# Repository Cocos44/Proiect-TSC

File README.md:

# Proiect InkTime - Smartwatch

Un smartwatch bazat pe microcontrollerul Nordic nRF52840 cu display e-Paper.

---

## Diagrama bloc

---

## Bill of Materials

| Ref | Componenta | Valoare | JLC Parts | Datasheet |
|-----|------------|---------|-----------|-----------|
| U1 | nRF52840 | $5.14 | [JLC](https://jlcpcb.com/parts/componentSearch?searchTxt=nRF52840-QF) | [DS](https://jlcpcb.com/api/file/downloadByFileSystemAccessId/8589839228197629952) |
| SWD | TC2030-IDC | $100.26 | [JLC](https://jlcpcb.com/partdetail/MicrochipTech-TC2030_CLIP3PACK/C5444772) | [DS](https://www.lcsc.com/datasheet/lcsc_datasheet_2403201318_Microchip-Tech-TC2030-CLIP-3PACK_C5444772.pdf) |
| ANT1 | 2450AT18B100E | $1.03 | [JLC](https://jlcpcb.com/partdetail/JohansonDielectrics-2450AT18B100E/C2917717) | [DS](https://jlcpcb.com/api/file/downloadByFileSystemAccessId/8588940948130156544) |
| X1 | NX2016SA-32MHZ-EXS00A-CS11336 | $9.04 | [JLC](https://jlcpcb.com/partdetail/NDK-NX2016SA_32MHZ_EXS00ACS11336/C6134317) | [DS](https://jlcpcb.com/api/file/downloadByFileSystemAccessId/8603064888214908928) |
| L2 | RC0402JR-070RL | $0.01 | [JLC](https://jlcpcb.com/partdetail/YAGEO-RC0402JR070RL/C60485) | [DS](https://jlcpcb.com/api/file/downloadByFileSystemAccessId/8717146932348461056) |
| L3 | RC0402JR-070RL | $0.01 | [JLC](https://jlcpcb.com/partdetail/YAGEO-RC0402JR070RL/C60485) | [DS](https://jlcpcb.com/api/file/downloadByFileSystemAccessId/8717146932348461056) |
| X2 | FC-135_32.7680KA-A3 | $0.2677 | [JLC](https://jlcpcb.com/partdetail/SeikoEpson-FC_135_32_7680KAA3/C2650472) | [DS](https://jlcpcb.com/partdetail/SeikoEpson-FC_135_32_7680KAA3/C2650472) |
| IC3 | BMA423 | $11.30 | [JLC](https://jlcpcb.com/partdetail/BoschSensortec-BMA423/C189517) | [DS](https://jlcpcb.com/api/file/downloadByFileSystemAccessId/8588894317147017216) |
| IC9 | RT6160 | $0.56 | [JLC](https://jlcpcb.com/partdetail/RichtekTech-RT6160AWSC/C7065276) | [DS](https://jlcpcb.com/api/file/downloadByFileSystemAccessId/8600398231234883584) |
| L7 | MLP2016SR47MT0S1 | $0.10 | [JLC](https://jlcpcb.com/partdetail/TDK-MLP2016SR47MT0S1/C87545) | [DS](https://jlcpcb.com/api/file/downloadByFileSystemAccessId/8588933367512879104) |
| IC1 | BQ25180YBGR | $2.01 | [JLC](https://jlcpcb.com/partdetail/TexasInstruments-BQ25180YBGR/C3682423) | [DS](https://www.ti.com/cn/lit/gpn/bq25180) |
| L5 | 744043680 | $9.53 | [JLC](https://jlcpcb.com/partdetail/WurthElektronik-744043680/C2045671) | [DS](https://www.we-online.com/components/products/datasheet/744043680.pdf) |
| D2 | MBR0530 | $0.03 | [JLC](https://jlcpcb.com/partdetail/78464-MBR0530/C77336) | [DS](https://jlcpcb.com/api/file/downloadByFileSystemAccessId/8586175081181818880) |
| D4 | MBR0530 | $0.03 | [JLC](https://jlcpcb.com/partdetail/78464-MBR0530/C77336) | [DS](https://jlcpcb.com/api/file/downloadByFileSystemAccessId/8586175081181818880) |
| D5 | MBR0530 | $0.03 | [JLC](https://jlcpcb.com/partdetail/78464-MBR0530/C77336) | [DS](https://jlcpcb.com/api/file/downloadByFileSystemAccessId/8586175081181818880) |
| Q3 | SI1308EDL-T1-GE3 | $0.18 | [JLC](https://jlcpcb.com/partdetail/VishayIntertech-SI1308EDL_T1GE3/C469327) | [DS](https://jlcpcb.com/api/file/downloadByFileSystemAccessId/8588884784742846464) |
| Q1 | DMG2305UX-7 | $0.10 | [JLC](https://jlcpcb.com/partdetail/DiodesIncorporated-DMG2305UX7/C150470) | [DS](https://jlcpcb.com/api/file/downloadByFileSystemAccessId/8560079443617075200) |
| IC2 | DRV2605YZFR | $1.31 | [JLC](https://jlcpcb.com/partdetail/TexasInstruments-DRV2605YZFR/C81079) | [DS](https://www.ti.com/cn/lit/gpn/drv2605) |
| D3 | USBLC6-2SC6Y | $0.24 | [JLC](https://jlcpcb.com/partdetail/STMicroelectronics-USBLC62SC6Y/C2969755) | [DS](https://jlcpcb.com/api/file/downloadByFileSystemAccessId/8603165824304111616) |
| J4 | KH-TYPE-C-16P | $0.08 | [JLC](https://jlcpcb.com/partdetail/Shenzhen_KinghelmElec-KH_TYPE_C16P/C709357) | [DS](https://jlcpcb.com/api/file/downloadByFileSystemAccessId/8588905154556923904) |
| U3 | MAX17048G-T10 | $2.44 | [JLC](https://jlcpcb.com/partdetail/2777647-MAX17048GT10/C2682616) | [DS](https://jlcpcb.com/api/file/downloadByFileSystemAccessId/8588907428524003328) |
| J1 | 503480-2400 | $0.84 | [JLC](https://jlcpcb.com/partdetail/MOLEX-5034802400/C122434) | [DS](https://www.molex.com/content/dam/molex/molex-dot-com/products/automated/en-us/salesdrawingpdf/503/503480/5034802400_sd.pdf?inline) |

---

## Descriere Functionalitate Hardware

### Microcontroller - nRF52840
 Caracteristici principale:
- ARM Cortex-M4 la 64 MHz
- 1MB Flash, 256KB RAM
- Bluetooth 5.0 / BLE integrat
- Radio 2.4GHz cu suport pentru antena externa
- Interfete multiple: SPI, I2C, UART, GPIO
 
### Display E-Paper - Waveshare 1.54" V2
 
Display-ul comunica prin SPI pe 4 fire:
- Rezolutie: 200x200 pixeli
- Consum ultra-redus - retine imaginea fara alimentare
- Conectat la nRF52840 prin conectorul FPC 24 pini (503480-2400)
 
### IMU - BMA423
 
Accelerometrul BMA423 comunica prin I2C:
- Accelerometru pe 3 axe
- Numarare pasi, recunoastere activitate
 
### Incarcator Baterie - BQ25180
 
BQ25180 gestioneaza incarcarea bateriei prin I2C:
- Intrare: USB-C 5V
- Iesire: 3.7V LiPo
- Curent maxim de incarcare: 250mA
 
### Baterie - AKYGA LP502030
 
- Dimensiuni: 32.5mm x 21mm x 5.5mm
- Conectata direct la doua test pad-uri de pe placa
 
### Motor Vibratii - FIT0774
 
- Controlat prin GPIO via driver haptic DRV2605
- Diametru: 10mm, Inaltime: 2.7mm
- Tensiune de operare: 1.5-4.2V
 
### Conector Debug - TC2030-IDC
 
- Conector Tag-Connect 10 pini
- Folosit pentru programare si debugging SWD
- Semnale: SWDIO, SWDCLK, GND, VCC, RESET
 
---
 
## Pinii nRF52840
 
| Pin nRF52840 | Semnal | Componenta | Interfata |
|--------------|--------|-----------|-----------|
| P0.00/XL1 | XL1 | Crystal X2 (32.768kHz) | XTAL |
| P0.01/XL2 | XL2 | Crystal X2 (32.768kHz) | XTAL |
| P0.05/AIN3 | EPD_CS | E-Paper (J1 FPC) | SPI CS |
| P0.06 | SDA | BMA423, BQ25180, MAX17048, DRV2605 | I2C SDA |
| P0.07 | SCL | BMA423, BQ25180, MAX17048, DRV2605 | I2C SCL |
| P0.08 | IMU_INT1 | BMA423 | GPIO Input |
| P1.08 | IMU_INT2 | BMA423 | GPIO Input |
| P0.11 | PMIC_INT | BQ25180 | GPIO Input |
| P0.12 | HAPTIC_EN | DRV2605 | GPIO |
| VBUS | VBUS | USB-C (J4) | Power |
| D- | D- | USB-C (J4) / USBLC6 | USB |
| D+ | D+ | USB-C (J4) / USBLC6 | USB |
| P0.13 | SW_UP | Buton Up | GPIO Input |
| P0.14 | SW_ENT | Buton Enter | GPIO Input |
| P0.15 | EPD_DC | E-Paper (J1 FPC) | SPI DC |
| P0.16 | EPD_RST | E-Paper (J1 FPC) | GPIO |
| P0.17 | EPD_BUSY | E-Paper (J1 FPC) | GPIO Input |
| P0.18/RESET | RESET | TC2030-IDC | SWD/GPIO |
| SWDCLK | SWDCLK | TC2030-IDC | SWD |
| SWDIO | SWDIO | TC2030-IDC | SWD |
| P1.02 | SW_DN | Buton Down | GPIO Input |
| P0.10/NFC2 | ALERT | MAX17048 | GPIO Input |
| ANT | RF | Antena 2450AT18B100E | RF |
| P0.02/AIN0 | SCK | E-Paper (J1 FPC) | SPI SCK |
| P0.03/AIN1 | MOSI | E-Paper (J1 FPC) | SPI MOSI |
 
---

## Jurnal de Design si Pasi de Implementare (Design Log)

### Pasi realizare PCB
* Plasarea componentelor majore: Am inceput prin a pozitiona componentele mari si cele cu constrangeri mecanice stricte (mufa USB, butoanele laterale, conectorul de display si microcontrollerul). Imediat dupa plasarea componentelor principale, am legat componentele mici (condensatoare, rezistente, etc.). In final, am pus Polygon Pour pe toate planurile infara de cel de POWER.

* Dupa plasarea componentelor in PCB, am inceput rutarea mai intai cu traseele de putere, urmand dupa cu restul.

* Rutarea (Top/Bottom): Traseele au fost rutate evitand unghiurile drepte. Liniile de alimentare au fost dimensionate cu latimea de 0.3mm (variind sub zonele dense BGA/QFN), iar cele de date la 0.15mm. Zona de sub antena radio a fost curatata complet de cupru si semnale.

### Erori DRC acceptate
* Copper Clearance: In zona pad-urilor BGA ale nRF52840, distanta minima dintre pad-uri este impusa de producator si nu poate fi modificata. Erorile sunt inevitabile si acceptate de JLCPCB.

* Overlap: Aceste erori apar din cauza tehnicii Via-in-Pad. Via-urile plasate direct in pad-urile componentei se suprapun geometric cu traseele adiacente.

* Drill Size: Via-urile folosite pentru Via-in-Pad au diametrul mai mic decat minimul din regulile DRC standard, ales intentionat pentru a incapea in pad-urile mici ale nRF52840.

* Board Outline Clearance. Erori de la mufa USB-C.
---

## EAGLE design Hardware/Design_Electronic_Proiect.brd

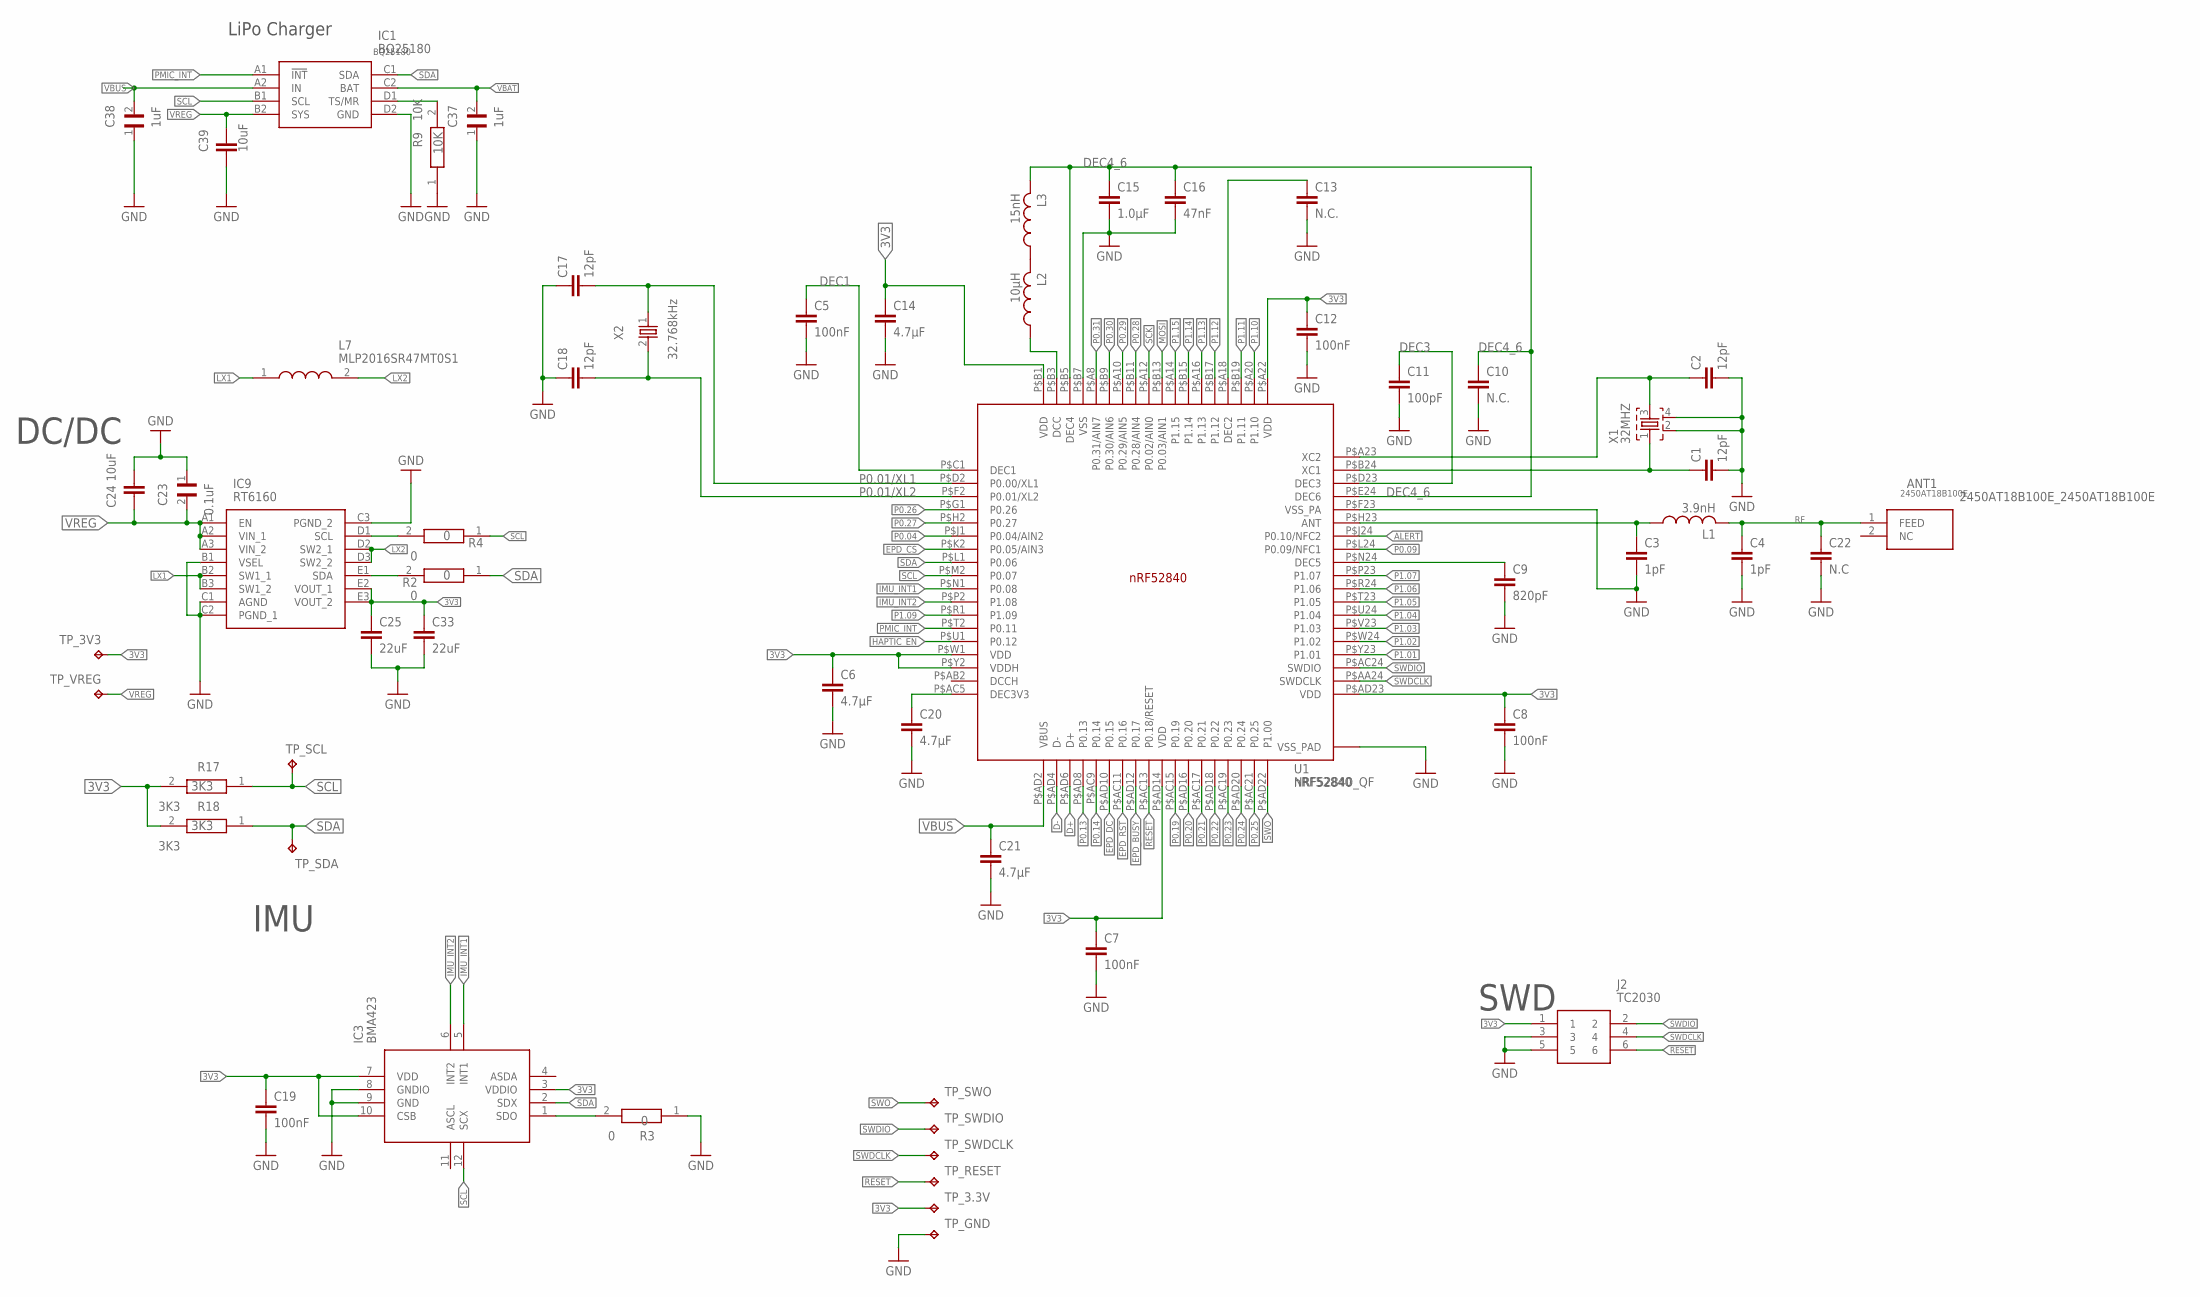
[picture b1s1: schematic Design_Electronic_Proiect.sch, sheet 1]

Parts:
ANT1: 2450AT18B100E_2450AT18B100E; 2450AT18B100E_ANTC3216X140N
C1, C2, C17, C18: 12pF; NORDIC_NRF_3_RESC0201_L
C3, C4: 1pF; NORDIC_NRF_3_RESC0201_L
C5, C7, C8, C12: 100nF; NORDIC_NRF_3_RESC0201_L
C6, C14, C20, C21: 4.7µF; NORDIC_NRF_3_RESC0201_L
C9: 820pF; NORDIC_NRF_3_RESC0201_L
C10, C13: N.C.; NORDIC_NRF_3_RESC0201_L
C11: 100pF; NORDIC_NRF_3_RESC0201_L
C15: 1.0µF; NORDIC_NRF_3_RESC0201_L
C16: 47nF; NORDIC_NRF_3_RESC0201_L
C19: 100nF; NORDIC_NRF_3_RESC0402_L
C22: N.C; NORDIC_NRF_3_RESC0201_L
C23: 0.1uF; GRM011R60J152KE01L_2_CAPC0201X13N
C24, C39: 10uF; NORDIC_NRF_3_RESC0402_L
C25, C33: 22uF; NORDIC_NRF_3_RESC0402_L
C37, C38: 1uF; GRM011R60J152KE01L_2_CAPC0201X13N
IC1: BQ25180; BQ25180YBGR_BGA8C40P2X4_100X155X50
IC3: BMA423; BMA423_BMA423
IC9: RT6160; RT6160AWSC_BGA15C40P3X5_140X230X60
J2: TC2030; TC2030-IDC_TC2030IDC
L1: 3.9nH; NORDIC_NRF_2_RESC0402_L
L2: 10µH; NORDIC_NRF_2_RESC0402_L
L3: 15nH; NORDIC_NRF_2_RESC0402_L
L7: MLP2016SR47MT0S1; MLP2016SR47MT0S1_INDC2016X100N
R2, R3, R4: 0; CPF0201D7K68C1_0201
R9: 10K; CPF0201D7K68C1_0201
R17, R18: 3K3; CPF0201D7K68C1_0201
TP_3.3V, TP_3V3: HECTOR_WATCH_1_TPTP20R; HECTOR_WATCH_1_TP20R
TP_GND: HECTOR_WATCH_1_TPTP20R; HECTOR_WATCH_1_TP20R
TP_RESET: HECTOR_WATCH_1_TPTP20R; HECTOR_WATCH_1_TP20R
TP_SCL: HECTOR_WATCH_1_TPTP20R; HECTOR_WATCH_1_TP20R
TP_SDA: HECTOR_WATCH_1_TPTP20R; HECTOR_WATCH_1_TP20R
TP_SWDCLK: HECTOR_WATCH_1_TPTP20R; HECTOR_WATCH_1_TP20R
TP_SWDIO: HECTOR_WATCH_1_TPTP20R; HECTOR_WATCH_1_TP20R
TP_SWO: HECTOR_WATCH_1_TPTP20R; HECTOR_WATCH_1_TP20R
TP_VREG: HECTOR_WATCH_1_TPTP20R; HECTOR_WATCH_1_TP20R
U1: nRF52840; NORDIC_NRF_4_AQFN50P700X700X85_HS-74N
X1: 32MHZ; NORDIC_NRF_BT-XTAL_2016_N
X2: 32.768kHz; NORDIC_NRF_1_XTAL_3215_N

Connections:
3V3: C6.1, C7.1, C8.1, C12.1, C14.1, C19.1, C25.1, C33.1, IC3.3 (VDDIO), IC3.7 (VDD), IC3.10 (CSB), IC9.E2 (VOUT_1), IC9.E3 (VOUT_2), J2.1, R17.2, R18.2, TP_3.3V.TP, TP_3V3.TP, U1.P$A22 (VDD), U1.P$AD14 (VDD), U1.P$AD23 (VDD), U1.P$B1 (VDD), U1.P$W1 (VDD), U1.P$Y2 (VDDH); also elsewhere on the board
ALERT: U1.P$J24 (P0.10/NFC2); also elsewhere on the board
D+: U1.P$AD6 (D+); also elsewhere on the board
D-: U1.P$AD4 (D-); also elsewhere on the board
DEC1: C5.1, U1.P$C1 (DEC1)
DEC3: C11.1, U1.P$D23 (DEC3)
DEC4_6: C10.1, C15.1, C16.1, L3.2, U1.P$B5 (DEC4), U1.P$E24 (DEC6)
EPD_BUSY: U1.P$AD12 (P0.17); also elsewhere on the board
EPD_CS: U1.P$K2 (P0.05/AIN3); also elsewhere on the board
EPD_DC: U1.P$AD10 (P0.15); also elsewhere on the board
EPD_RST: U1.P$AC11 (P0.16); also elsewhere on the board
GND: C1.2, C2.2, C3.2, C4.2, C5.2, C6.2, C7.2, C8.2, C9.2, C10.2, C11.2, C12.2, C13.2, C14.2, C15.2, C16.2, C17.1, C18.1, C19.2, C20.2, C21.2, C22.2, C23.1, C24.1, C25.2, C33.2, C37.1, C38.1, C39.2, IC1.D2 (GND), IC3.8 (GNDIO), IC3.9 (GND), IC9.B1 (VSEL), IC9.C1 (AGND), IC9.C2 (PGND_1), IC9.C3 (PGND_2), J2.3, J2.5, R3.1, R9.1, TP_GND.TP, U1.P$74 (VSS_PAD), U1.P$75 (VSS_PAD), U1.P$76 (VSS_PAD), U1.P$77 (VSS_PAD), U1.P$78 (VSS_PAD), U1.P$79 (VSS_PAD), U1.P$80 (VSS_PAD), U1.P$81 (VSS_PAD), U1.P$82 (VSS_PAD), U1.P$83 (VSS_PAD), U1.P$84 (VSS_PAD), U1.P$85 (VSS_PAD), U1.P$86 (VSS_PAD), U1.P$87 (VSS_PAD), U1.P$88 (VSS_PAD), U1.P$89 (VSS_PAD), U1.P$90 (VSS_PAD), U1.P$B7 (VSS), U1.P$F23 (VSS_PA), X1.2, X1.4; also elsewhere on the board
HAPTIC_EN: U1.P$U1 (P0.12); also elsewhere on the board
IMU_INT1: IC3.5 (INT1), U1.P$N1 (P0.08)
IMU_INT2: IC3.6 (INT2), U1.P$P2 (P1.08)
LX1: IC9.B2 (SW1_1), IC9.B3 (SW1_2), L7.1
LX2: IC9.D2 (SW2_1), IC9.D3 (SW2_2), L7.2
MOSI: U1.P$B13 (P0.03/AIN1); also elsewhere on the board
unnamed: C20.1, U1.P$AC5 (DEC3V3)
unnamed: C9.1, U1.P$N24 (DEC5)
unnamed: C3.1, L1.1, U1.P$H23 (ANT)
unnamed: C1.1, U1.P$B24 (XC1), X1.1
unnamed: C2.1, U1.P$A23 (XC2), X1.3
unnamed: L2.1, U1.P$B3 (DCC)
unnamed: L2.2, L3.1
unnamed: C13.1, U1.P$A18 (DEC2)
unnamed: IC1.D1 (TS/MR), R9.2
unnamed: IC9.D1 (SCL), R4.2
unnamed: IC9.E1 (SDA), R2.2
unnamed: IC3.1 (SDO), R3.2
P0.01/XL1: C17.2, U1.P$D2 (P0.00/XL1), X2.1
P0.01/XL2: C18.2, U1.P$F2 (P0.01/XL2), X2.2
P0.04: U1.P$J1 (P0.04/AIN2)
P0.09: U1.P$L24 (P0.09/NFC1)
P0.13: U1.P$AD8 (P0.13); also elsewhere on the board
P0.14: U1.P$AC9 (P0.14); also elsewhere on the board
P0.19: U1.P$AC15 (P0.19)
P0.20: U1.P$AD16 (P0.20)
P0.21: U1.P$AC17 (P0.21)
P0.22: U1.P$AD18 (P0.22)
P0.23: U1.P$AC19 (P0.23)
P0.24: U1.P$AD20 (P0.24)
P0.25: U1.P$AC21 (P0.25)
P0.26: U1.P$G1 (P0.26)
P0.27: U1.P$H2 (P0.27)
P0.28: U1.P$B11 (P0.28/AIN4)
P0.29: U1.P$A10 (P0.29/AIN5)
P0.30: U1.P$B9 (P0.30/AIN6)
P0.31: U1.P$A8 (P0.31/AIN7)
P1.01: U1.P$Y23 (P1.01); also elsewhere on the board
P1.02: U1.P$W24 (P1.02); also elsewhere on the board
P1.03: U1.P$V23 (P1.03)
P1.04: U1.P$U24 (P1.04)
P1.05: U1.P$T23 (P1.05)
P1.06: U1.P$R24 (P1.06)
P1.07: U1.P$P23 (P1.07)
P1.09: U1.P$R1 (P1.09)
P1.10: U1.P$A20 (P1.10)
P1.11: U1.P$B19 (P1.11)
P1.12: U1.P$B17 (P1.12)
P1.13: U1.P$A16 (P1.13)
P1.14: U1.P$B15 (P1.14)
P1.15: U1.P$A14 (P1.15)
PMIC_INT: IC1.A1 (!INT), U1.P$T2 (P0.11)
RESET: J2.6, TP_RESET.TP, U1.P$AC13 (P0.18/RESET)
RF: ANT1.1 (FEED), C4.1, C22.1, L1.2
SCK: U1.P$A12 (P0.02/AIN0); also elsewhere on the board
SCL: IC1.B1 (SCL), IC3.12 (SCX), R4.1, R17.1, TP_SCL.TP, U1.P$M2 (P0.07); also elsewhere on the board
SDA: IC1.C1 (SDA), IC3.2 (SDX), R2.1, R18.1, TP_SDA.TP, U1.P$L1 (P0.06); also elsewhere on the board
SWDCLK: J2.4, TP_SWDCLK.TP, U1.P$AA24 (SWDCLK)
SWDIO: J2.2, TP_SWDIO.TP, U1.P$AC24 (SWDIO)
SWO: TP_SWO.TP, U1.P$AD22 (P1.00)
VBAT: C37.2, IC1.C2 (BAT); also elsewhere on the board
VBUS: C21.1, C38.2, IC1.A2 (IN), U1.P$AD2 (VBUS); also elsewhere on the board
VREG: C23.2, C24.2, C39.1, IC1.B2 (SYS), IC9.A1 (EN), IC9.A2 (VIN_1), IC9.A3 (VIN_2), TP_VREG.TP

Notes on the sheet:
LiPo Charger
DC/DC
IMU
SWD

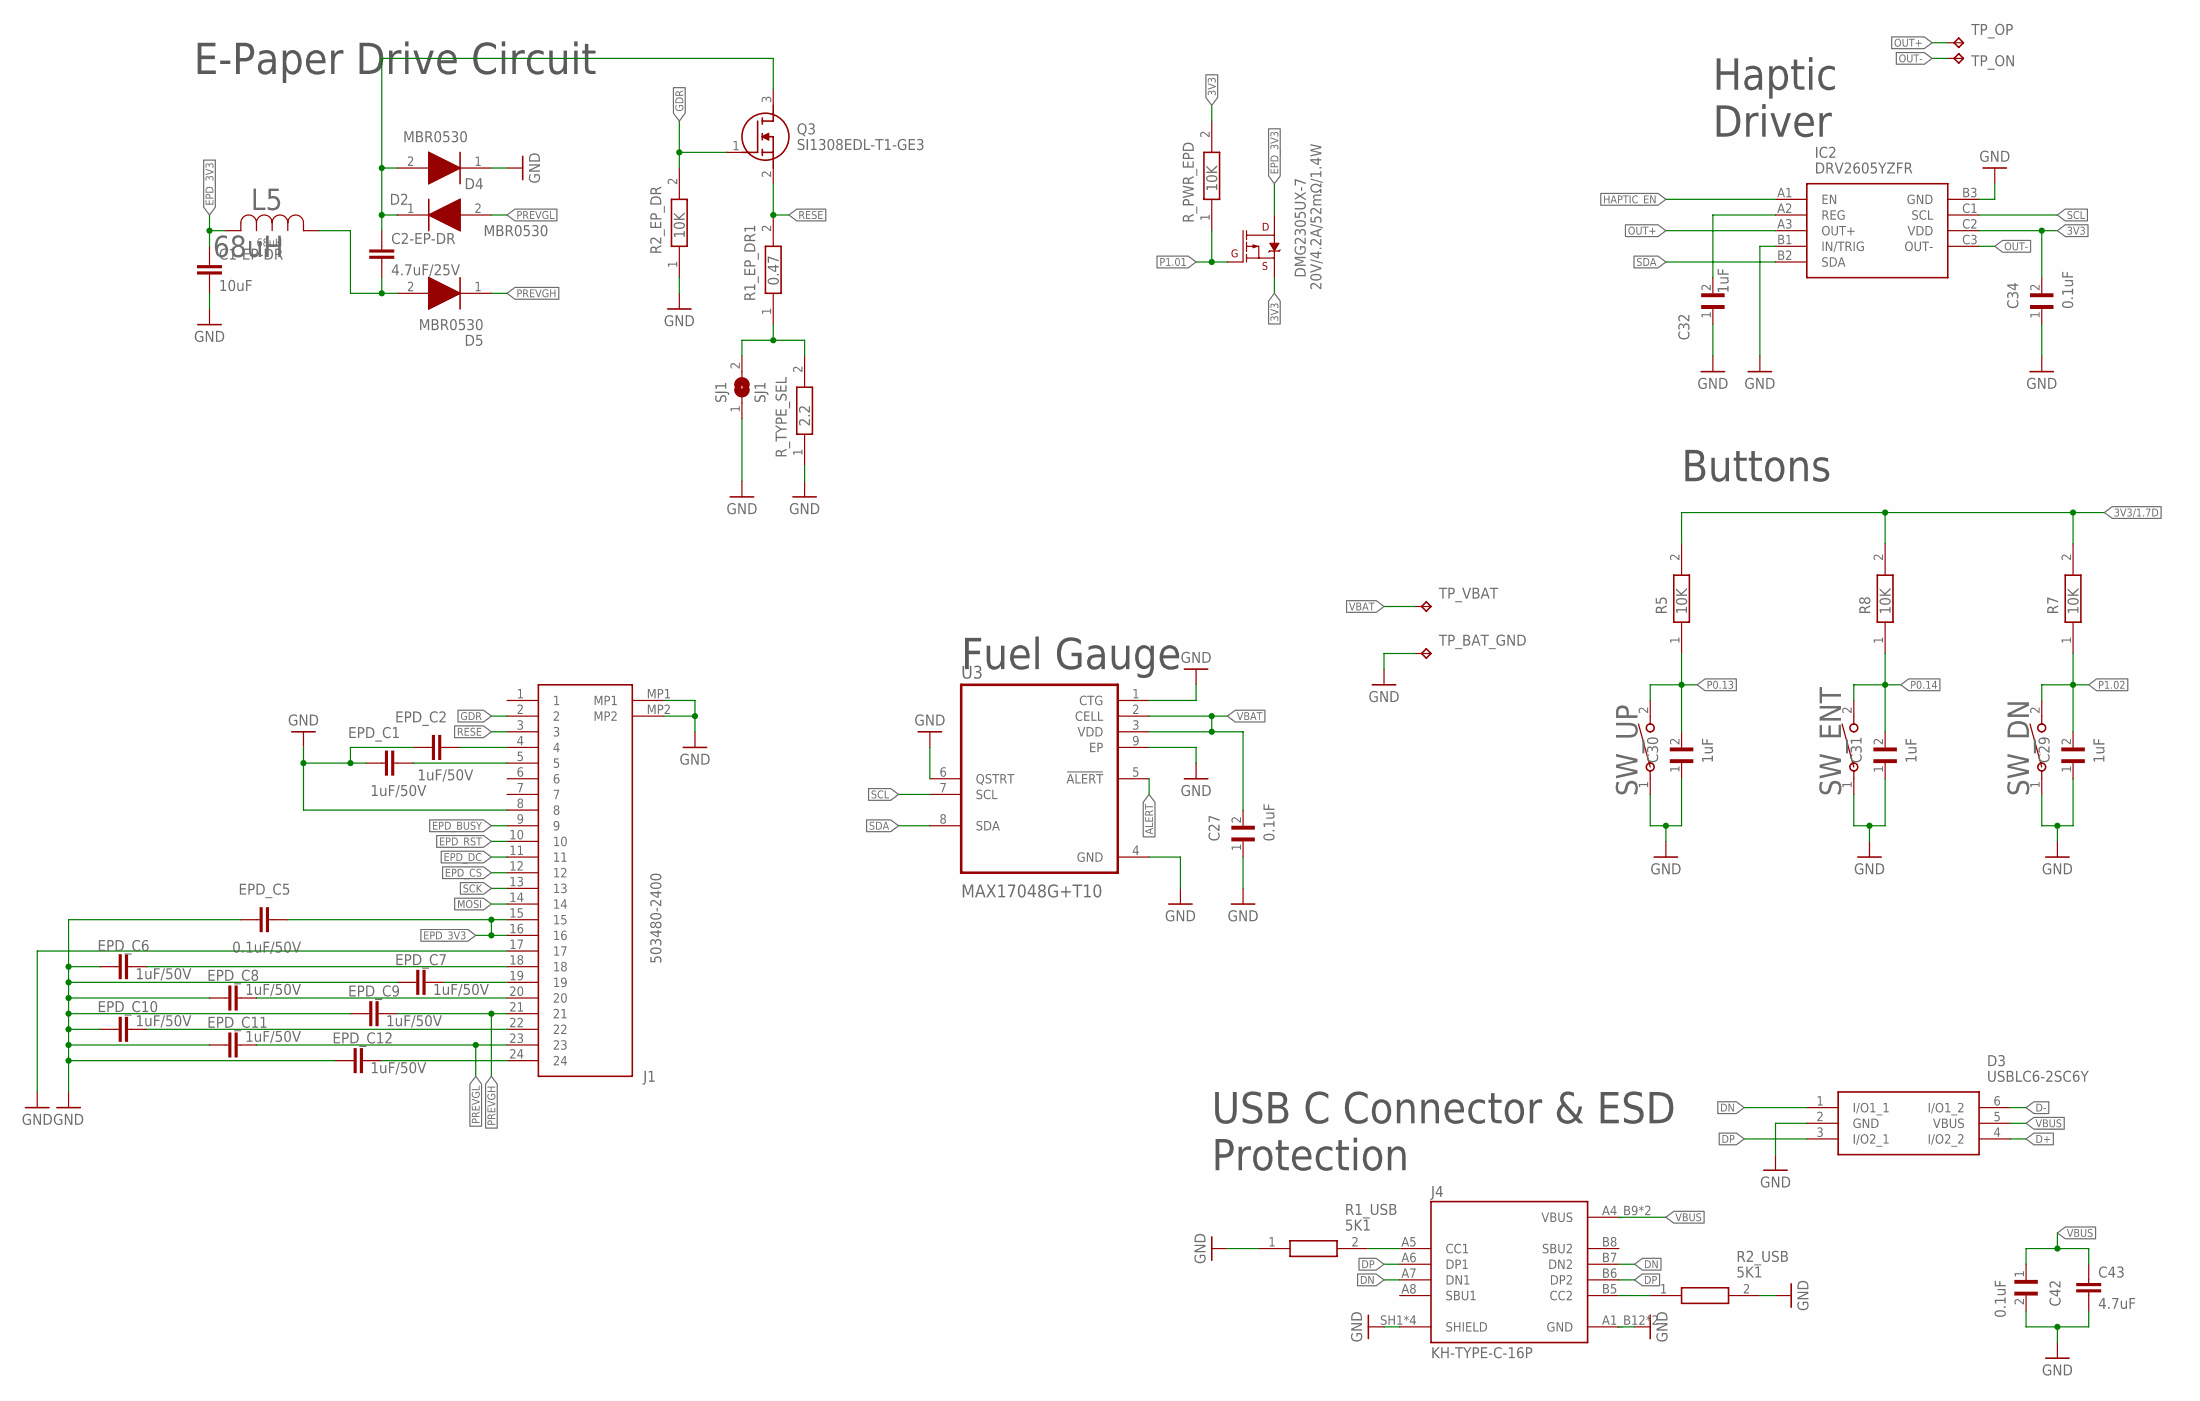
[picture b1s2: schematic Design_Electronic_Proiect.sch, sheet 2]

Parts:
C1-EP-DR: 10uF; NORDIC_NRF_3_RESC0402_L
C2-EP-DR: 4.7uF/25V; NORDIC_NRF_3_RESC0402_L
C27, C34, C42: 0.1uF; GRM011R60J152KE01L_2_CAPC0201X13N
C29, C30, C31, C32: 1uF; GRM011R60J152KE01L_2_CAPC0201X13N
C43: 4.7uF; NORDIC_NRF_3_RESC0402_L
D2, D4, D5: MBR0530; ESP32_C6_LIBRARY_5_SOD3716X135N
D3: USBLC6-2SC6Y; ESP32_C6_LIBRARY_3_SOT95P280X145-6N
DMG2305UX-7: 20V/4.2A/52mΩ/1.4W; ESP32_C6_LIBRARY_4_ESP32_C6_LIBRARY_4_ESP32_C6_LIBRARY_4_ES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
EPD_C1, EPD_C2, EPD_C6, EPD_C7, EPD_C8, EPD_C9, EPD_C10, EPD_C11, EPD_C12: 1uF/50V; NORDIC_NRF_3_RESC0402_L
EPD_C5: 0.1uF/50V; NORDIC_NRF_3_RESC0402_L
IC2: DRV2605YZFR; DRV2605YZFR_BGA9C50P3X3_144X144X62
J1: 503480-2400; 503480-2400_5034802400
J4: KH-TYPE-C-16P; KH-TYPE-C-16P_KINGHELM_KH-TYPE-C-16P
L5: 68uH; ESP32_C6_LIBRARY_2_IND_4828-WE-TPC_WRE
Q3: SI1308EDL-T1-GE3; ESP32_C6_LIBRARY_6_SOT65P210X110-3N
R1_EP_DR1: 0.47; CPF0201D7K68C1_0201
R1_USB, R2_USB: 5K1; CPF0201D7K68C1_0201
R2_EP_DR, R5, R7, R8: 10K; CPF0201D7K68C1_0201
R_PWR_EPD: 10K; CPF0201D7K68C1_0201
R_TYPE_SEL: 2.2; CPF0201D7K68C1_0201
SJ1: SJ1; ESP32_C6_LIBRARY_7_JUMPER_SJ
SW_DN: 2025-10-22_07-23-44_LIBRARY_EVP-AKE31ASW_EVP-AKE3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; 2025-10-22_07-23-44_LIBRARY_SW_EVP-AKE31A_PAN
SW_ENT: 2025-10-22_07-23-44_LIBRARY_EVP-AKE31ASW_EVP-AKE3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; 2025-10-22_07-23-44_LIBRARY_SW_EVP-AKE31A_PAN
SW_UP: 2025-10-22_07-23-44_LIBRARY_EVP-AKE31ASW_EVP-AKE3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; 2025-10-22_07-23-44_LIBRARY_SW_EVP-AKE31A_PAN
TP_BAT_GND: HECTOR_WATCH_1_TPTP20R; HECTOR_WATCH_1_TP20R
TP_ON: HECTOR_WATCH_1_TPTP20R; HECTOR_WATCH_1_TP20R
TP_OP: HECTOR_WATCH_1_TPTP20R; HECTOR_WATCH_1_TP20R
TP_VBAT: HECTOR_WATCH_1_TPTP20R; HECTOR_WATCH_1_TP20R
U3: MAX17048G+T10; ESP32_C6_LIBRARY_SON50P200X200X80-9N

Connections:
3V3: C34.2, DMG2305UX-7.2 (S), IC2.C2 (VDD), R_PWR_EPD.2; also elsewhere on the board
3V3/1.7D: R5.2, R7.2, R8.2
ALERT: U3.5 (!ALERT); also elsewhere on the board
D+: D3.4 (I/O2_2); also elsewhere on the board
D-: D3.6 (I/O1_2); also elsewhere on the board
DN: D3.1 (I/O1_1), J4.A7 (DN1), J4.B7 (DN2)
DP: D3.3 (I/O2_1), J4.A6 (DP1), J4.B6 (DP2)
EPD_3V3: C1-EP-DR.1, DMG2305UX-7.3 (D), EPD_C5.2, J1.15, J1.16, L5.2
EPD_BUSY: J1.9; also elsewhere on the board
EPD_CS: J1.12; also elsewhere on the board
EPD_DC: J1.11; also elsewhere on the board
EPD_RST: J1.10; also elsewhere on the board
GDR: J1.2, Q3.1 (G), R2_EP_DR.2
GND: C1-EP-DR.2, C27.1, C29.1, C30.1, C31.1, C32.1, C34.1, C42.2, C43.2, D3.2 (GND), D4.1 (K), EPD_C1.1, EPD_C2.1, EPD_C5.1, EPD_C6.1, EPD_C7.1, EPD_C8.1, EPD_C9.1, EPD_C10.1, EPD_C11.1, EPD_C12.1, IC2.B1 (IN/TRIG), IC2.B3 (GND), J1.8, J1.17, J1.MP1, J1.MP2, J4.A1_B12 (GND), J4.A12_B1 (GND), J4.SH1 (SHIELD), J4.SH2 (SHIELD), J4.SH3 (SHIELD), J4.SH4 (SHIELD), R1_USB.1, R2_EP_DR.1, R2_USB.2, R_TYPE_SEL.1, SJ1.1, SW_DN.1, SW_ENT.1, SW_UP.1, TP_BAT_GND.TP, U3.1 (CTG), U3.4 (GND), U3.6 (QSTRT), U3.9 (EP); also elsewhere on the board
HAPTIC_EN: IC2.A1 (EN); also elsewhere on the board
MOSI: J1.14; also elsewhere on the board
unnamed: C2-EP-DR.2, D5.2 (A), L5.1
unnamed: C2-EP-DR.1, D2.1 (K), D4.2 (A), Q3.3 (D)
unnamed: R1_EP_DR1.1, R_TYPE_SEL.2, SJ1.2
unnamed: C32.2, IC2.A2 (REG)
unnamed: J4.A5 (CC1), R1_USB.2
unnamed: EPD_C2.2, J1.4
unnamed: J4.B5 (CC2), R2_USB.1
unnamed: EPD_C1.2, J1.5
unnamed: EPD_C6.2, J1.18
unnamed: EPD_C7.2, J1.19
unnamed: EPD_C8.2, J1.20
unnamed: EPD_C10.2, J1.22
unnamed: EPD_C12.2, J1.24
OUT+: IC2.A3 (OUT+), TP_OP.TP
OUT-: IC2.C3 (OUT-), TP_ON.TP
P0.13: C30.2, R5.1, SW_UP.2; also elsewhere on the board
P0.14: C31.2, R8.1, SW_ENT.2; also elsewhere on the board
P1.01: DMG2305UX-7.1 (G), R_PWR_EPD.1; also elsewhere on the board
P1.02: C29.2, R7.1, SW_DN.2; also elsewhere on the board
PREVGH: D5.1 (K), EPD_C9.2, J1.21
PREVGL: D2.2 (A), EPD_C11.2, J1.23
RESE: J1.3, Q3.2 (S), R1_EP_DR1.2
SCK: J1.13; also elsewhere on the board
SCL: IC2.C1 (SCL), U3.7 (SCL); also elsewhere on the board
SDA: IC2.B2 (SDA), U3.8 (SDA); also elsewhere on the board
VBAT: C27.2, TP_VBAT.TP, U3.2 (CELL), U3.3 (VDD); also elsewhere on the board
VBUS: C42.1, C43.1, D3.5 (VBUS), J4.A4_B9 (VBUS), J4.A9_B4 (VBUS); also elsewhere on the board

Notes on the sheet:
E-Paper Drive Circuit
Haptic Driver
Buttons
Fuel Gauge
USB C Connector & ESD Protection

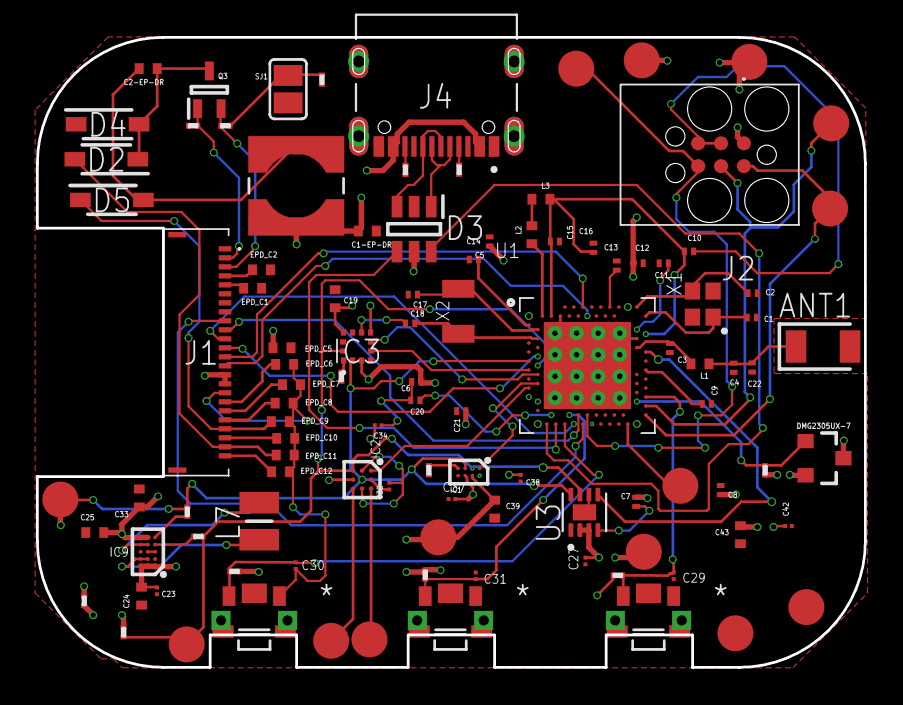
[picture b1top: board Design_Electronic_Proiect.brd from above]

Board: 2 copper layers, 46.0 x 35.0 mm, 105 parts (0 on the bottom side), 71 nets.

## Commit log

2026-03-29 Created Hardware directory containing electrical scheme and 2D PCB
2026-03-29 Created Mechanical directory containing exploded view and full design.
2026-03-29 Worken on some mistakes on PCB. Created BOM and Pick and Place.
2026-03-29 Solved BOM and pick and place name issue.
2026-03-29 Adaugare imagini proiect.
2026-03-29 Added block diagram.
2026-03-29 Removed corrupted png file.
2026-03-29 Added correct diagram block.
2026-03-29 Expand README with hardware details and design log
    Added detailed hardware functionality descriptions and design log.

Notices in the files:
parts and their libraries:
COPYRIGHT: Copyright (C) 2024 Ultra Librarian. All rights reserved.
COPYRIGHT: Copyright (C) 2025 Ultra Librarian. All rights reserved.
